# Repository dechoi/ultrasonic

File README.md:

# ultrasonic
C Program sensor Ultrasonic HCSR-04 dengan AVR Microcontroller ATMEGA32
Pengukur jarak Digital menggunakan sensor ultrasonic  HC-SR04 dan AVR Microcontroller
Dalam tutorial ini kita akan membahas dan merancang rangkaian untuk mengukur jarak. Sirkuit ini dikembangkan dengan menghubungkan sensor ultrasonik "HC-SR04" dengan mikrokontroler AVR ATMEGA32 . Sensor ini menggunakan teknik yang disebut "ECHO" yang merupakan sesuatu yang Anda dapatkan saat suara dipantulkan kembali setelah dipantulkan dari permukaan.
Kita tahu getaran suara tidak bisa menembus benda padat / solid. Jadi apa yang terjadi adalah, ketika sebuah sumber suara menghasilkan getaran yang sinyal suara tempuh melalui udara pada kecepatan 220 meter per detik. Getaran ini saat sinyal suara bertemu telinga kita, kita menggambarkannya sebagai suara. Seperti yang dikatakan tadi getaran ini tidak bisa menembus solid, jadi saat sinyal suara memancar dengan permukaan seperti dinding, sinyal suara dipantulkan kembali pada kecepatan yang sama dengan sumbernya, yang disebut ECHO.

Seperti yang ditunjukkan pada gambar, pada awalnya kita perlu melakukan sensor untuk mengukur jarak, yaitu sinyal logika HIGH / TINGGI pada pin pemicu sensor lebih dari 10uS, setelah itu getaran suara dikirim oleh sensor, setelah gema, sensor memberikan sebuah sinyal pada pin output yang proporsinya sebanding dengan jarak antara sumber dan rintangan.
Rumus jarak ( FISIKA ) adalah S = 340 .t / s
Jarak ini dihitung sebagai, jarak (dalam cm) = lebar output pulsa (dalam uS) / 58.
Di sini lebar sinyal harus diambil dalam kelipatan uS (mikro detik atau 10 ^ -6).
Komponen yang dibutuhkan
Perangkat keras: ATMEGA32, Power supply (12v), AVR-ISP PROGRAMMER, DISPLAY LCD (16x2LCD), kapasitor 100uF, resistor 10KΩ (2 buah), sensor HC-SR04.
Perangkat lunak: AVR GCC,Notepad Programmer, dan Progis.  Disini kita menggunakan PORTC untuk terhubung ke port data LCD (D0-D7). Siapa pun yang tidak ingin bekerja dengan FUSE BITS dari ATMEGA32A tidak dapat menggunakan PORTC, karena PORTC berisi jenis komunikasi khusus yang hanya dapat dinonaktifkan dengan mengubah FUSEBITS. ( dalam ujicoba ini kita abaikan saja paragraf ini, namun perlu dipelajari cara setting Fuse Bit )
Pada rangkaian, Anda amati hanya digunakan dua pin kontrol, ini memberi fleksibilitas pemahaman yang lebih baik. Bit kontras dan READ / WRITE tidak sering digunakan sehingga bisa disingkat menjadi ground. Ini menempatkan LCD dalam mode kontras dan baca tertinggi. Kita hanya perlu mengendalikan pin ENABLE dan RS untuk mengirim karakter dan data yang sesuai.
PERHATIKAN GAMBAR untuk Sensor Ultrasonic PIN TRIGGER pada PD0  dan PIN ECHO pada PD2

Sambungan yang dilakukan untuk LCD diberikan di bawah ini:
•	PIN1 atau VSS ke ground
•	PIN2 atau Vdd atau VCC ke 5 v
•	PIN3 atau VEE ke ground (memberikan kontras maksimal)
•	PIN4 atau RS (Register Selection) ke PD6 dari UC
•	PIN5 atau RW (Baca / Tulis) ke ground (letakkan LCD dalam mode baca)
•	PIN6 atau E (Enable) ke PD5 dari UC
•	PIN7 atau D0 sampai PC0 dari UC
•	PIN8 atau D1 ke PC1 dari UC
•	PIN9 atau D2 ke PC2 dari UC
•	PIN10 atau D3 ke PC3 dari UC
•	PIN11 atau D4 sampai PC4 dari UC
•	PIN12 atau D5 sampai PC5 dari UC
•	PIN13 atau D6 sampai PC6 dari UC
•	PIN14 atau D7 sampai PC7 dari UC
Di sirkuit Anda dapat melihat bahwa kita telah menggunakan komunikasi 8bit (D0-D7) namun ini bukan keharusan dan kita dapat menggunakan komunikasi 4bit (D4-D7) namun dengan program komunikasi 4 bit menjadi agak rumit. Jadi seperti yang ditunjukkan pada tabel di atas kita menghubungkan 10 pin LCD ke controller dimana 8 pin adalah pin data dan 2 pin untuk kontrol.
 Sensor ultrasonik adalah perangkat empat pin, PIN1- VCC atau + 5V; PIN2-TRIGGER; PIN3- ECHO; PIN4- GROUND. Trigger pin adalah tempat kita memberi trigger untuk memberi tahu sensor untuk mengukur jarak. Echo adalah pin output dimana kita mendapatkan jarak dalam bentuk lebar pulsa. Pin gema disini terhubung ke controller sebagai sumber interupsi eksternal. Jadi untuk mendapatkan lebar keluaran sinyal, pin gema sensor terhubung ke INT0 (interrupt 0) atau PD2.

Tiga register di atas harus diatur agar pengaturannya berjalan dan kita akan membahasnya secara singkat,
BLUE (INT0): bit ini harus disetel tinggi untuk mengaktifkan interrupt0 eksternal, setelah pin ini diset, kita bisa merasakan perubahan logika pada pin PIND2.
BROWN (ISC00, ISC01): kedua bit ini disesuaikan dengan perubahan logika yang sesuai pada PD2, yang dianggap sebagai interrupt.
 
Jadi seperti yang dikatakan sebelumnya kita perlu interupsi untuk memulai penghitungan dan untuk menghentikannya. Jadi kita tetapkan ISC00 sebagai satu dan kita mendapatkan interupsi bila ada logika LOW/ RENDAH ke HIGH di INT0;  Interupsi lain bila ada logika HIGH to LOW.
RED (CS10): Bit ini hanya untuk mengaktifkan dan menonaktifkan counter. Meski bekerja sama dengan bit CS10 lainnya, CS12. Kami tidak melakukan prescaling apapun di sini, jadi kami tidak perlu khawatir tentang sinyal suara.
Beberapa hal penting yang perlu diingat disini adalah:
Kami menggunakan jam internal ATMEGA32A yang 1MHz. Tidak ada prescaling disini, kita tidak melakukan compare match interrupt menghasilkan rutinitas, jadi tidak ada setting register yang rumit.
Nilai penghitungan setelah penghitungan disimpan dalam register TCNT1 16bit,
Paham ...? mari kita mulai Coding...

Kami menggunakan AVRGCC untuk kopilasi kode C, jika menggunakan OS Windows 7, win 8, win 10 tambahkan library sysmin.dll pada folder UTIL dalam aplikasi AVRGCC, karena akan ditemui ERROR jika tidak disertakan,

Ayoo berkreasi...

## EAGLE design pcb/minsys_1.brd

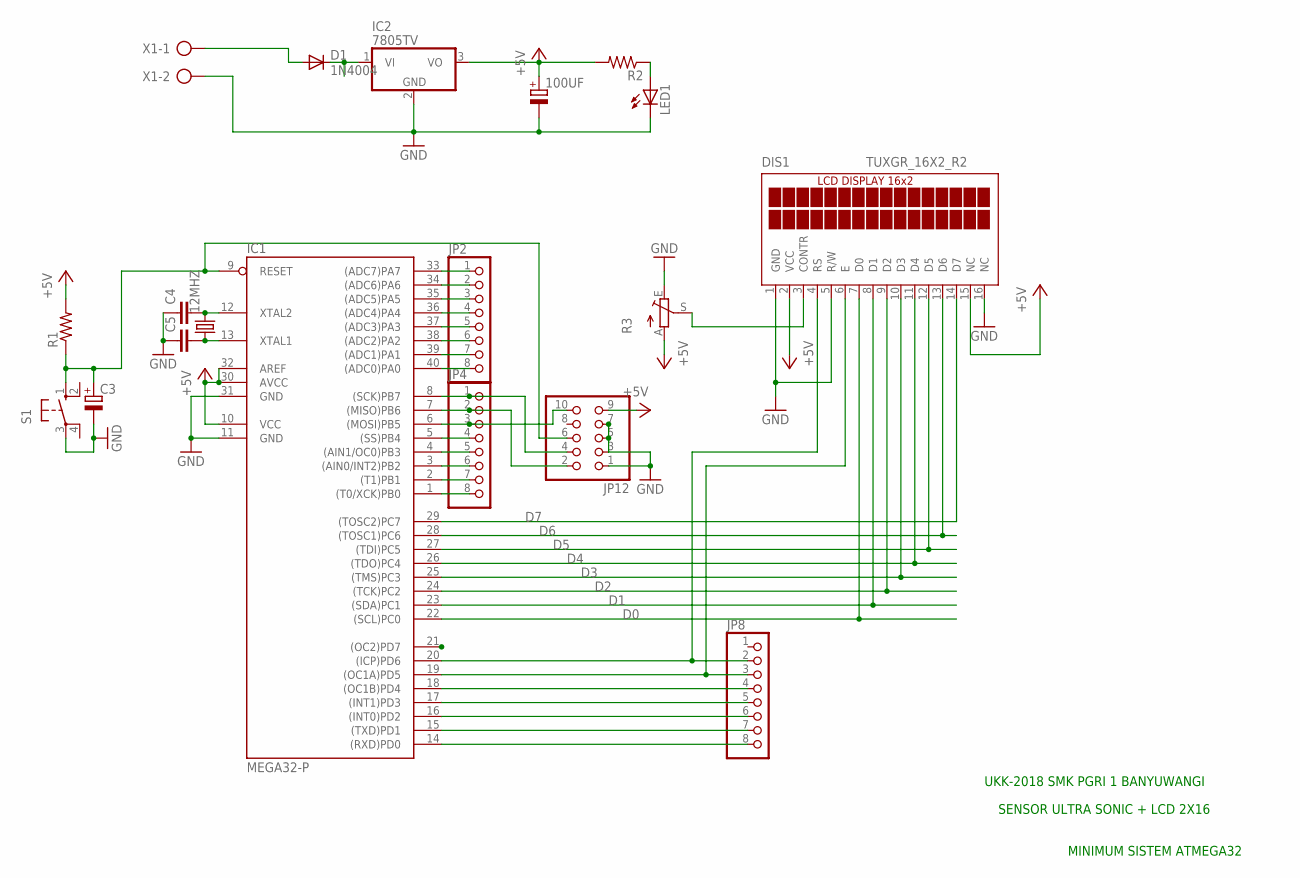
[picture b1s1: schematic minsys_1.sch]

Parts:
12MHZ: CRYSTALHC49S; HC49/S
100UF: CPOL-EUE2.5-5; E2,5-5
C3: CPOL-EUE2-5; E2-5
C4, C5: C-EU050-024X044; C050-024X044
D1: 1N4004; DO41-10
DIS1: TUXGR_16X2_R2
IC1: MEGA32-P; DIL40
IC2: 7805TV; TO220V
JP2, JP4, JP8: PINHD-1X8; 1X08
JP12: PINHD-2X5; 2X05
LED1: LED3MM
R1, R2: R-US_0207/10; 0207/10
R3: TRIM_EU-RS3; RS3
S1: 10-XX; B3F-10XX
X1: AK300/2

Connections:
+5V: 100UF.+, DIS1.2 (VCC), DIS1.15 (NC), IC1.10 (VCC), IC1.30 (AVCC), IC1.32 (AREF), IC2.3 (VO), JP12.9, R1.2, R2.2, R3.A
D0: DIS1.7 (D0), IC1.22 ((SCL)PC0)
D1: DIS1.8 (D1), IC1.23 ((SDA)PC1)
D2: DIS1.9 (D2), IC1.24 ((TCK)PC2)
D3: DIS1.10 (D3), IC1.25 ((TMS)PC3)
D4: DIS1.11 (D4), IC1.26 ((TDO)PC4)
D5: DIS1.12 (D5), IC1.27 ((TDI)PC5)
D6: DIS1.13 (D6), IC1.28 ((TOSC1)PC6)
D7: DIS1.14 (D7), IC1.29 ((TOSC2)PC7)
GND: 100UF.-, C3.-, C4.1, C5.1, DIS1.1 (GND), DIS1.5 (R/W), DIS1.16 (NC), IC1.11 (GND), IC1.31 (GND), IC2.2 (GND), JP12.1, JP12.3, JP12.5, JP12.7, LED1.K (C), R3.E, S1.3, X1.2
unnamed: 12MHZ.2, C4.2, IC1.12 (XTAL2)
unnamed: 12MHZ.1, C5.2, IC1.13 (XTAL1)
unnamed: C3.+, IC1.9 (RESET), JP12.6, R1.1, S1.1 (S)
unnamed: IC1.33 ((ADC7)PA7), JP2.1
unnamed: IC1.34 ((ADC6)PA6), JP2.2
unnamed: IC1.35 ((ADC5)PA5), JP2.3
unnamed: IC1.36 ((ADC4)PA4), JP2.4
unnamed: IC1.37 ((ADC3)PA3), JP2.5
unnamed: IC1.38 ((ADC2)PA2), JP2.6
unnamed: IC1.39 ((ADC1)PA1), JP2.7
unnamed: IC1.40 ((ADC0)PA0), JP2.8
unnamed: IC1.7 ((MISO)PB6), JP4.2, JP12.2
unnamed: IC1.6 ((MOSI)PB5), JP4.3, JP12.10
unnamed: IC1.5 ((SS)PB4), JP4.4
unnamed: IC1.4 ((AIN1/OC0)PB3), JP4.5
unnamed: IC1.3 ((AIN0/INT2)PB2), JP4.6
unnamed: IC1.2 ((T1)PB1), JP4.7
unnamed: IC1.1 ((T0/XCK)PB0), JP4.8
unnamed: DIS1.3 (CONTR), R3.S
unnamed: DIS1.4 (RS), IC1.20 ((ICP)PD6), JP8.2
unnamed: DIS1.6 (E), IC1.19 ((OC1A)PD5), JP8.3
unnamed: IC1.18 ((OC1B)PD4), JP8.4
unnamed: IC1.17 ((INT1)PD3), JP8.5
unnamed: IC1.16 ((INT0)PD2), JP8.6
unnamed: IC1.15 ((TXD)PD1), JP8.7
unnamed: IC1.14 ((RXD)PD0), JP8.8
unnamed: D1.A, X1.1
unnamed: D1.C, IC2.1 (VI)
unnamed: LED1.A, R2.1
unnamed: IC1.8 ((SCK)PB7), JP4.1, JP12.4

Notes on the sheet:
MINIMUM SISTEM ATMEGA32
SENSOR ULTRA SONIC + LCD 2X16
UKK-2018 SMK PGRI 1 BANYUWANGI

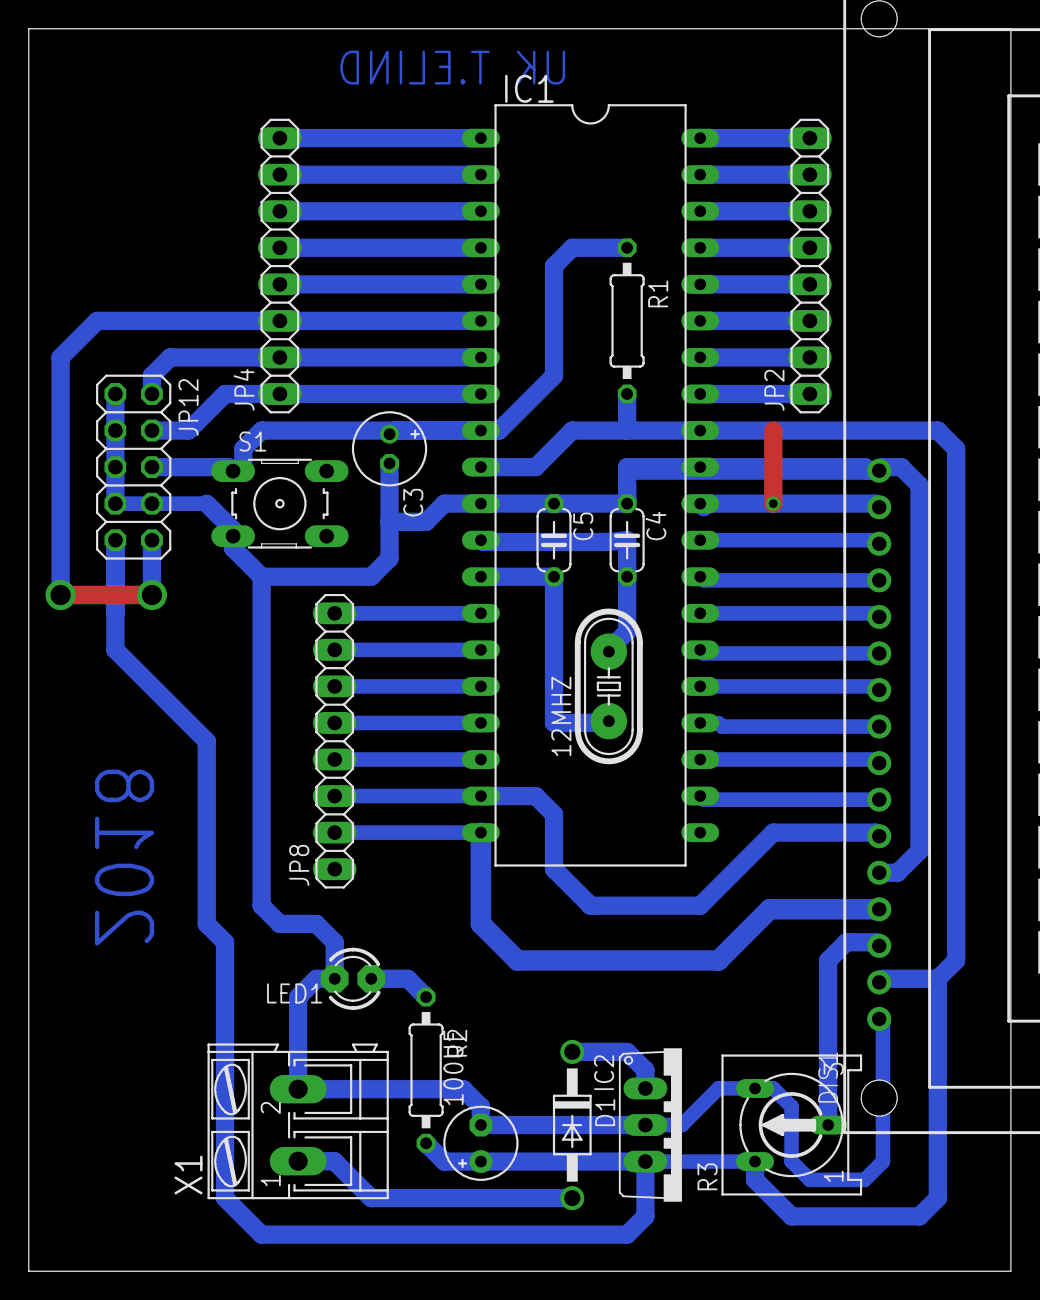
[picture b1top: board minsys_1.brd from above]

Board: 2 copper layers, 68.2 x 86.3 mm, 19 parts (0 on the bottom side), 40 nets.

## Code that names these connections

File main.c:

/*
C Program sensor Ultrasonic HCSR-04 dengan AVR Microcontroller
- LCD 8 BIT
- ATMEGA32
- UKK 2018 SMK PGRI 1 BANYUWANGI
- LCD DATA pada Port C
- Kontrol LCD pada Port D ( RS ==>PD6, RW==>GND, EN==>PD5 )
- Sensor Ultrasonic Triger Pin =PD0 , ECHO Pin = PD2 (INT0)
 */ 

#include <avr/io.h>
#include <avr/interrupt.h>
#include <util/delay.h>
#include <stdlib.h>

#define enable  5
#define register_num 6

void kirim_perintah_LCD(unsigned char command);
void kirim_karakter_LCD(unsigned char character);
void kirim_string_LCD(char *string_of_characters);

static volatile int pulse = 0;
static volatile int i = 0;

int main(void)
{
    //DDRA = 0xFF;
    DDRC = 0xFF;//LCD DATA
    DDRD = 0b11111011;//LCD CONTROL DAN SENSOR TRIGER pada bit LSB
    _delay_ms(50);
    
    GICR|=(1<<INT0);//enabling interrupt0
    MCUCR|=(1<<ISC00);//setting interrupt triggering logic change
    
    TCCR1A = 0;
    
    int16_t HITUNG = 0;//storing digital output
    char TAMPIL [16];
    

    kirim_perintah_LCD(0x01); //Clear Screen 0x01 = 00000001
    _delay_ms(50);
    kirim_perintah_LCD(0x38);// setting  16X2 LCD mode 8bit 
    _delay_ms(50);
    kirim_perintah_LCD(0b00001111);
    _delay_ms(50);
    
    sei();
    
    while(1)
    {
        PORTD|=(1<<PINC0);
        _delay_us(15);//trigger sensor untuk 15 uS ( mikro detik )
        PORTD &=~(1<<PINC0);
        
        /*perhitungan rumus Jarak , kecepatan, dan waktu
		V= 340 m/s
		V= 0,034 cm/uS
		Time = distance / speed
		t=s/v
		t= 10/ 0,034 = 294 uS
		distance = t x 0,034 / 2
		
		*/
		HITUNG = pulse * 0.024 /20;		
		
        
			if (HITUNG < 0){
				kirim_string_LCD ("Error           ");//jumlah karakter 16
				kirim_perintah_LCD(0x80 + 0x40 + 0);
			}
			else {
				kirim_string_LCD ("UKK ELIND 2018");
				kirim_perintah_LCD(0x80 + 0x40 + 0);
				kirim_string_LCD ("JARAK=");
				itoa(HITUNG,TAMPIL,10);
				/*ITOA mengubah nilai integer menjadi string,
				dan konversi menjadi desimal 
				*/
				kirim_string_LCD(TAMPIL);  
				kirim_string_LCD ("cm    ");
				kirim_perintah_LCD(0x80 + 0); //kembali ke kolom 1 dan baris 1
		
		}
		

    }
}

ISR(INT0_vect)//interrupt  routine
{
    if (i==1)//when logic from HIGH to LOW
    {
        TCCR1B=0;//disabling counter
        pulse=TCNT1;//count memory is updated to integer
        TCNT1=0;//resetting the counter memory
        i=0;
    }
    if (i==0)
    {
        TCCR1B|=(1<<CS10);
        i=1;
    }
}

void kirim_perintah_LCD(unsigned char command)
{
    PORTC = command;
    PORTD &= ~ (1<<register_num);
    PORTD |= 1<<enable;
    _delay_ms(8);
    PORTD &= ~1<<enable;
    PORTC = 0;
}

void kirim_karakter_LCD(unsigned char character)
{
    PORTC = character;
    PORTD |= 1<<register_num;
    PORTD |= 1<<enable;
    _delay_ms(8);
    PORTD &= ~1<<enable;
    PORTC = 0;
}
void kirim_string_LCD(char *string_of_characters)
{
    while(*string_of_characters > 0)
    {
        kirim_karakter_LCD(*string_of_characters++);
    }
}

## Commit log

2018-02-18 Add files
    perbaikan perhitungan rumus jarak
2018-02-18 Update Makefile
